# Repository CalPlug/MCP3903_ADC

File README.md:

# MCP3903_ADC

Project includes a demo board with info on driver for the Microchip Sigma-Delta ADC MCP3903.  Note: The board must have both the 3.3V and the 5V reference powered to operate.

An updated C library is included in this project as an update from the sample driver available from our MicrosemiSmartFusion2 Project:  https://github.com/CalPlug/Microsemi_SmartFusion2_FutureCreativeBoard_BaseDesign/blob/master/FCBBaseDesign/SoftConsole/FCBBaseDesign/src/MCP3909.c

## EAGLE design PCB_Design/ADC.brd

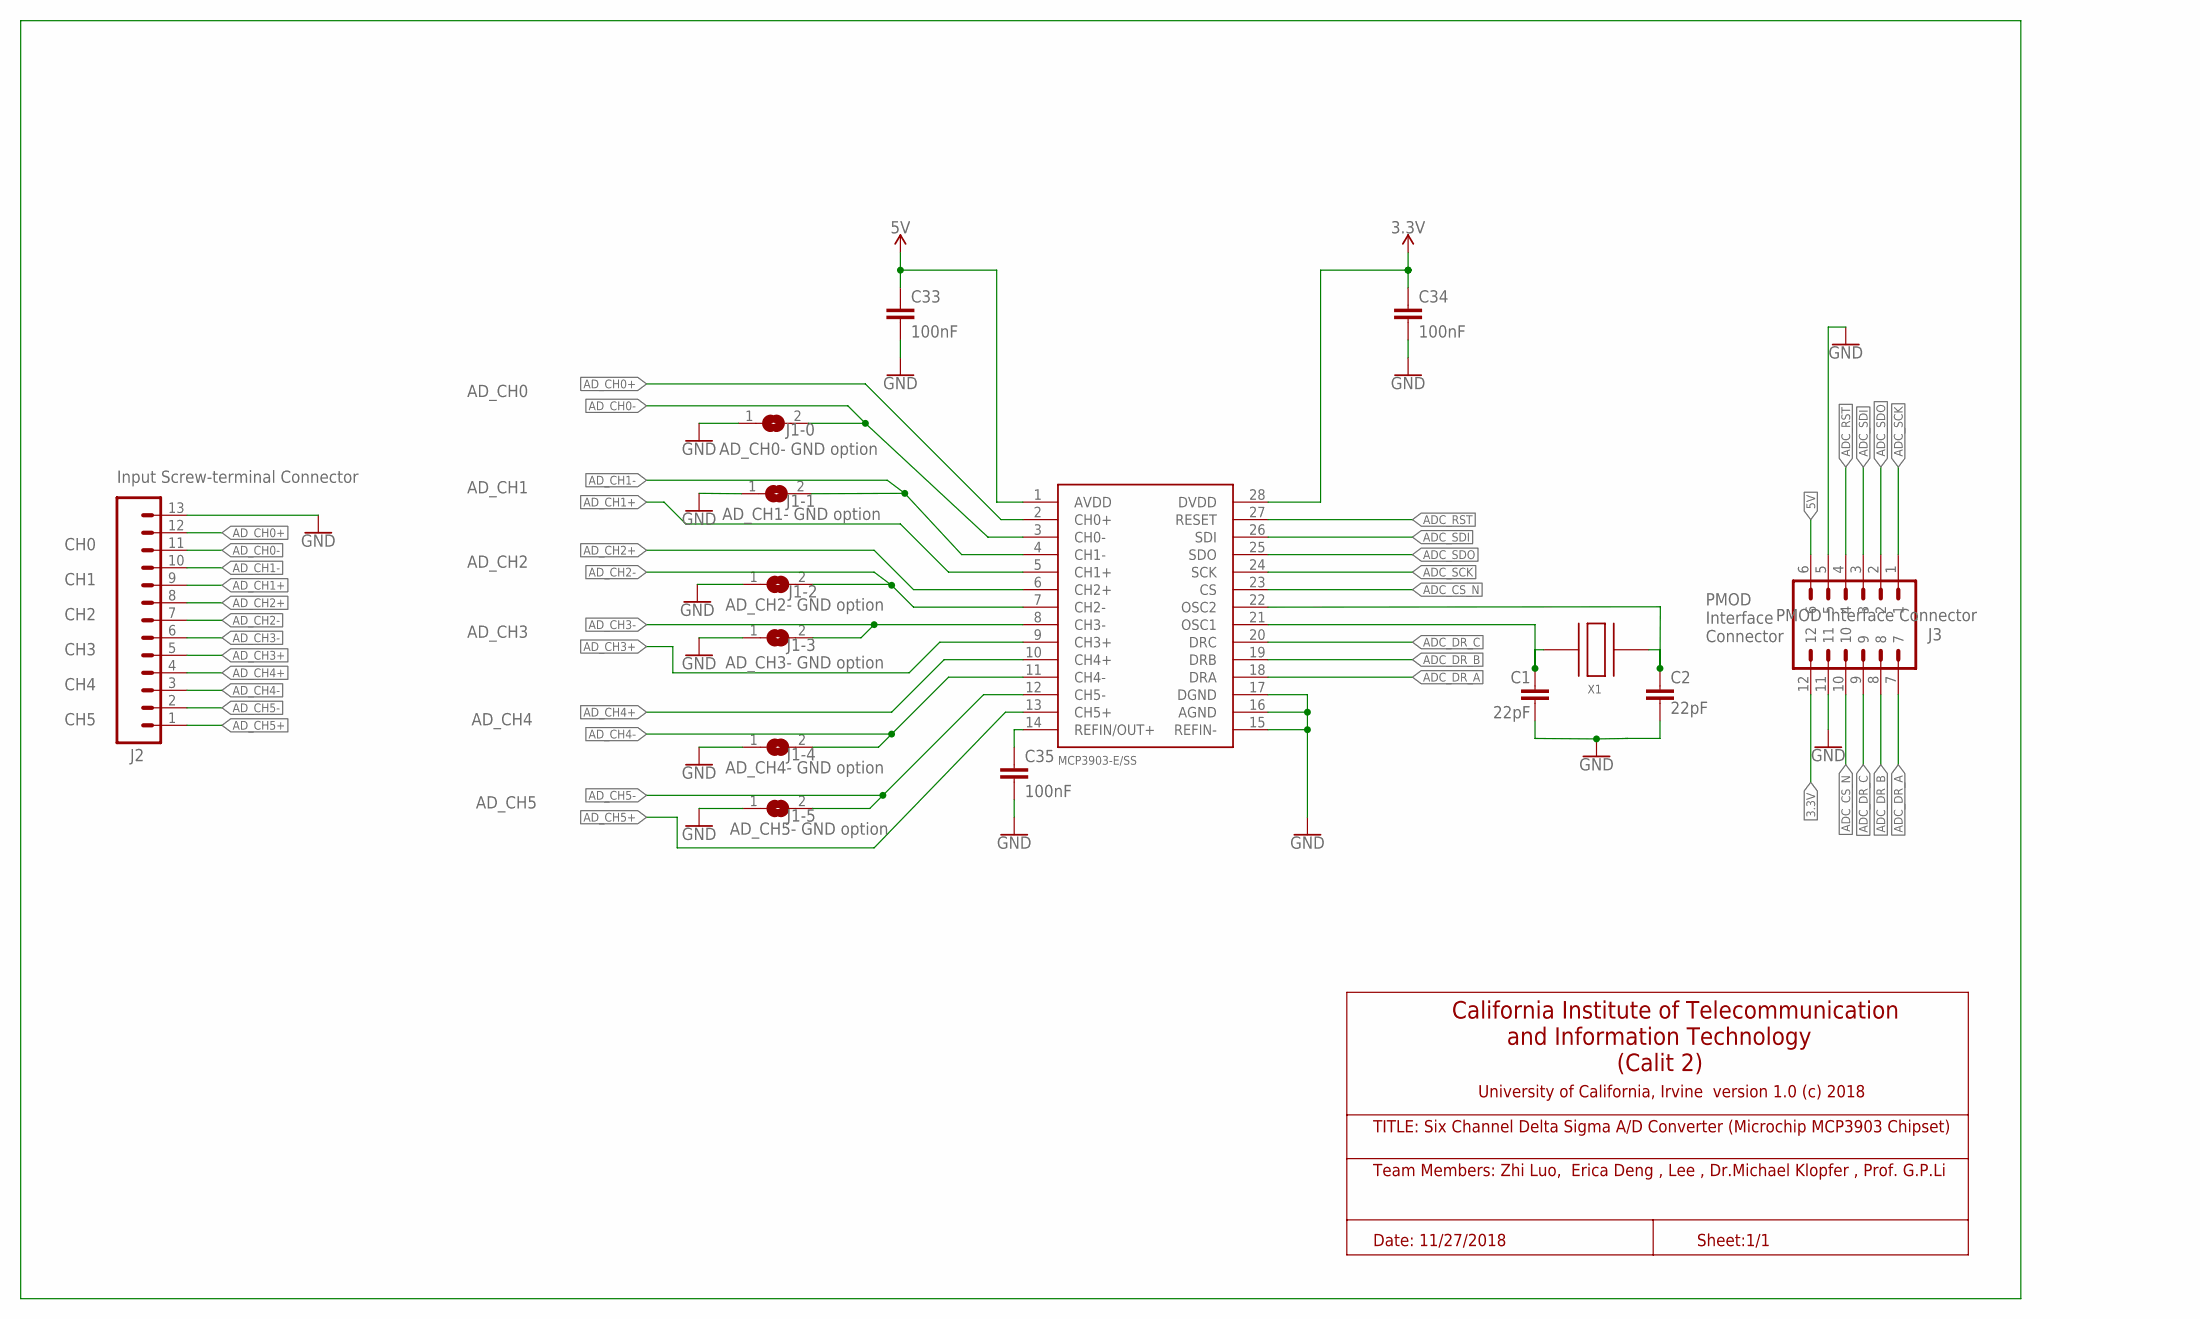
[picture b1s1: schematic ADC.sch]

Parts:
C1, C2: 22pF; 0603
C33, C34, C35: 100nF; C0603
J1-0: AD_CH0- GND option; SJ
J1-1: AD_CH1- GND option; SJ
J1-2: AD_CH2- GND option; SJ
J1-3: AD_CH3- GND option; SJ
J1-4: AD_CH4- GND option; SJ
J1-5: AD_CH5- GND option; SJ
J2: Input Screw-terminal Connector; 1X13
J3: PMOD Interface Connector; 2*6HEADER
U$1: MCP3903; 28-LEADSSOP
X1: 4MHZ; HC-49S

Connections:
3.3V: C34.1, J3.12, U$1.28 (DVDD); also elsewhere on the board
5V: C33.1, J3.6, U$1.1 (AVDD)
ADC_CS_N: J3.10, U$1.23 (CS)
ADC_DR_A: J3.7, U$1.18 (DRA)
ADC_DR_B: J3.8, U$1.19 (DRB)
ADC_DR_C: J3.9, U$1.20 (DRC)
ADC_RST: J3.4, U$1.27 (RESET); also elsewhere on the board
ADC_SCK: J3.1, U$1.24 (SCK)
ADC_SDI: J3.3, U$1.26 (SDI)
ADC_SDO: J3.2, U$1.25 (SDO)
AD_CH0+: J2.12, U$1.2 (CH0+)
AD_CH0-: J1-0.2, J2.11, U$1.3 (CH0-)
AD_CH1+: J2.9, U$1.5 (CH1+)
AD_CH1-: J1-1.2, J2.10, U$1.4 (CH1-)
AD_CH2+: J2.8, U$1.6 (CH2+)
AD_CH2-: J1-2.2, J2.7, U$1.7 (CH2-)
AD_CH3+: J2.5, U$1.9 (CH3+)
AD_CH3-: J1-3.2, J2.6, U$1.8 (CH3-)
AD_CH4+: J2.4, U$1.10 (CH4+)
AD_CH4-: J1-4.2, J2.3, U$1.11 (CH4-)
AD_CH5+: J2.1, U$1.13 (CH5+)
AD_CH5-: J1-5.2, J2.2, U$1.12 (CH5-)
GND: C1.2, C33.2, C34.2, C35.2, J1-0.1, J1-1.1, J1-2.1, J1-3.1, J1-4.1, J1-5.1, J2.13, J3.5, J3.11, U$1.15 (REFIN-), U$1.16 (AGND), U$1.17 (DGND)
unnamed: C35.1, U$1.14 (REFIN/OUT+)
OSC_1: C1.1, U$1.21 (OSC1), X1.1
OSC_2: C2.1, U$1.22 (OSC2), X1.2

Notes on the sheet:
California Institute of Telecommunication and Information Technology (Calit 2)
University of California, Irvine version 1.0 (c) 2018
TITLE: Six Channel Delta Sigma A/D Converter (Microchip MCP3903 Chipset)
Team Members: Zhi Luo, Erica Deng , Lee , Dr.Michael Klopfer , Prof. G.P.Li
Date: 11/27/2018
Sheet:1/1
CH0
CH1
CH2
CH3
CH4
CH5
AD_CH0
AD_CH1
AD_CH2
AD_CH3
AD_CH4
AD_CH5
PMOD Interface Connector

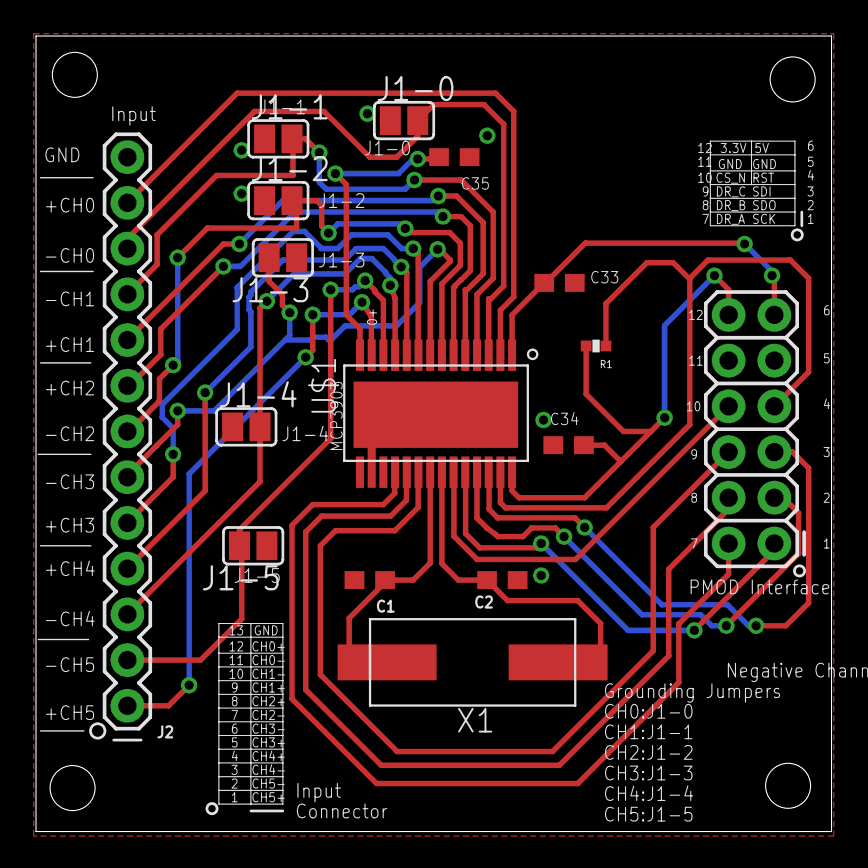
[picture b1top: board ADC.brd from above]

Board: 2 copper layers, 44.2 x 44.2 mm, 16 parts (0 on the bottom side), 26 nets.

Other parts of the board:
R1: 4.7k; 0402-RES

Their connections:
3.3V: R1.2; also elsewhere on the board
ADC_RST: R1.1; also elsewhere on the board

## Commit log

2019-02-14 Update Structure
2019-02-14 Update Folder Structure
2019-02-14 Update MCP3903 Arduino Library
2019-02-14 Update MCP3909.cpp
    Update variable types
2019-02-22 Create mcp3903example
2019-02-23 Update SPI Communication
2019-02-23 Update MCP3903.h
    Update Comments
2019-02-23 Update Edits
2019-02-23 Update SPI Speed
2019-02-23 Upldate LIb
2019-02-23 Update all channels in the example
2019-02-23 Update for all channels
2019-02-24 Create PCBlayout
2019-03-05 Update with Unsigned Char / Byte conver

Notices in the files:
parts and their libraries:
SparkFun-Connectors: Licensing: Creative Commons ShareAlike 4.0 International - https://creativecommons.org/licenses/by-sa/4.0
